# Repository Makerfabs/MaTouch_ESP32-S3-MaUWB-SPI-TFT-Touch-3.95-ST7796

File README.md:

# MaTouch ESP32-S3 MaUWB SPI TFT Touch 3.95" ST7796

## Introduction

The MaTouch 3.95 MaUWB is an ESP32-S3 development board featuring a 3.95-inch SPI display driven by the ST7796 controller, with a resolution of 480 x 320. It is equipped with an FT6236 capacitive touch controller, 16 MB Flash, and 8 MB PSRAM, providing responsive display and touch interaction for embedded applications.
The board integrates a MaUWB module for UWB ranging and indoor positioning applications. It also supports battery-powered operation, with an onboard lithium battery connector, charging circuit, battery level monitoring, and charge-status indicators, making it suitable for portable positioning terminals.
With its SPI display design, the board retains multiple GPIOs for secondary development through the expansion interface. It also includes a MicroSD card interface, native USB Type-C port, and USB-to-UART Type-C port for programming, debugging, and data storage.
Combining display, capacitive touch, UWB positioning, battery management, and expandable interfaces in one compact platform, the MaTouch 3.95 MaUWB is suitable for education, indoor positioning projects, embedded product development, and rapid prototyping.

Product Link: [MaTouch ESP32-S3 MaUWB SPI TFT Touch 3.95" ST7796](https://www.makerfabs.com/matouch-esp32-s3-mauwb-spi-tft-touch-3-95-st7796.html)

Wiki Link:  [MaTouch ESP32-S3 MaUWB SPI TFT Touch 3.95" ST7796](https://wiki.makerfabs.com/MaTouch%20ESP32_S3%20MaUWB%20SPI%20TFT%20Touch%203.95%27%27%20ST7796.html)

Example：1.[3.95_UWB_position](https://github.com/Makerfabs/MaTouch_ESP32-S3-MaUWB-SPI-TFT-Touch-3.95-ST7796#395_uwb_position)

## Features

- Controller: ESP32-S3 Chipset, 16MB Flash, 8MB PSRAM
- LCD: 3.95", 480X320 resolution 
- LCD Driver: ST7796
- LCD interface: SPI
- Touch Panel: Capacitive
- Touch Driver: FT6336U
- UWB: [MaUWB Chipset](https://www.makerfabs.com/mauwb-dw3000-chipset-ex-antenna-with-sma.html)
- RF band: CH5 (6489.6MHZ) 
- UWB rate: 850K/6.8M
- Max support: 8 Anchor 64 tags
- USB: 1 * USB_native, 1 *USB-to-UART
- USB-UART Driver: CH340K
- Power Supply: USB Type-C 5.0V(4.0V~5.25V)/ Lipo battery 
- Battery Charger
- Expansion interface: 2*JST1.25mm-4P
- LCD Backlight control: Yes

## Example

### 3.95_UWB_position

For details of this example, please refer to the [Wiki](https://wiki.makerfabs.com/MaTouch%20ESP32_S3%20MaUWB%20SPI%20TFT%20Touch%203.95%27%27%20ST7796.html#31-395_uwb_position) document.

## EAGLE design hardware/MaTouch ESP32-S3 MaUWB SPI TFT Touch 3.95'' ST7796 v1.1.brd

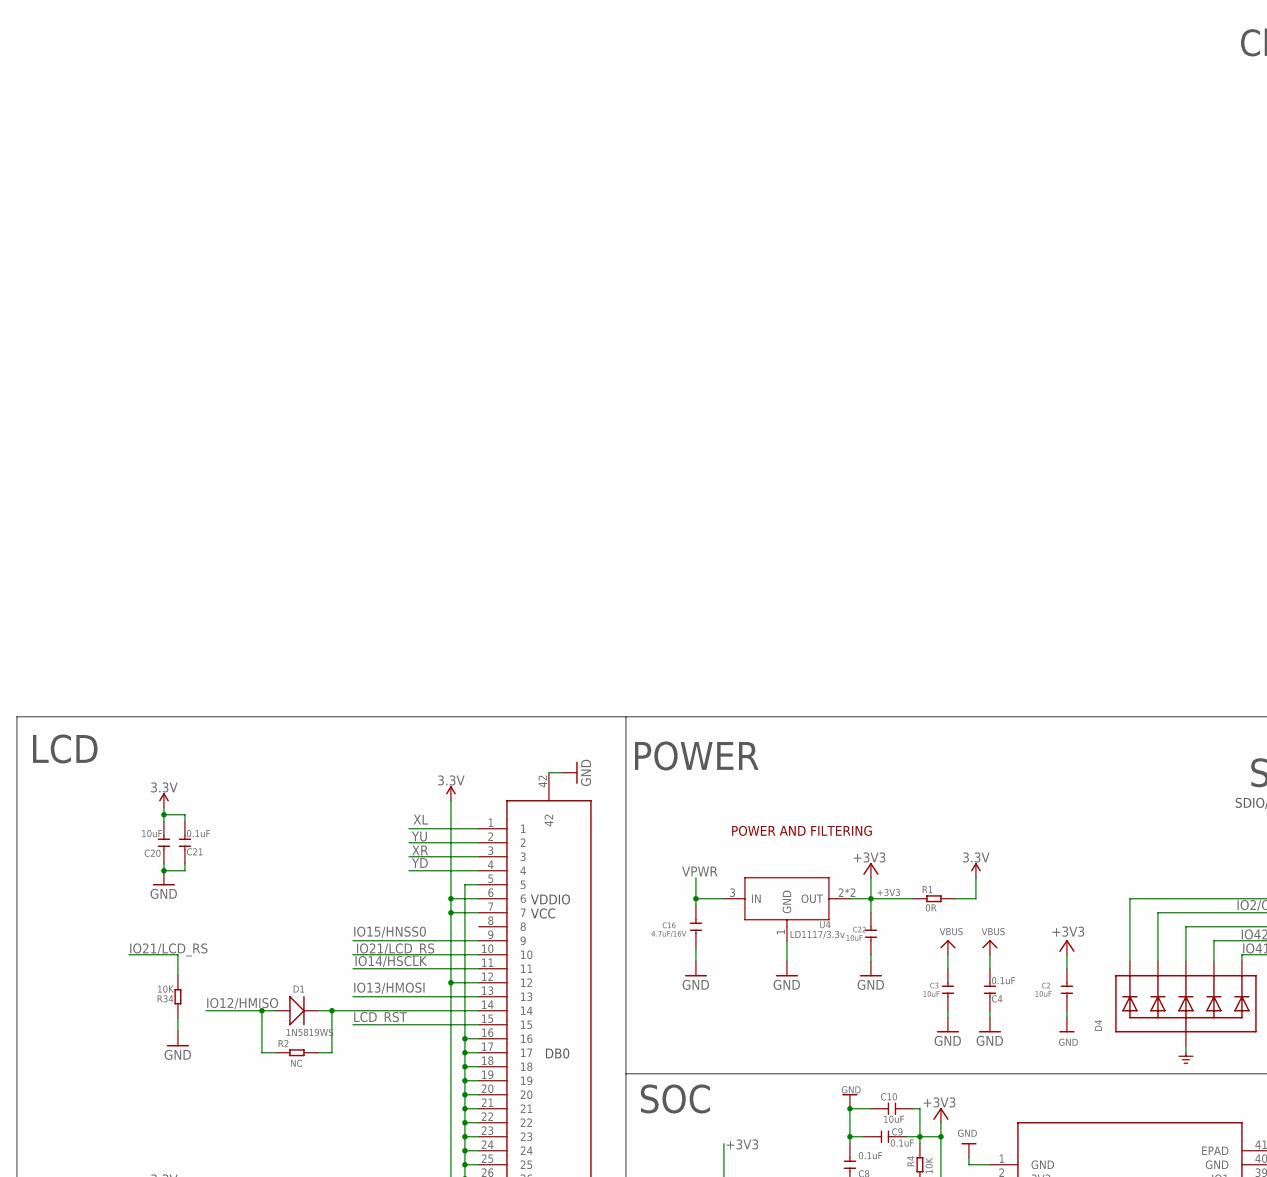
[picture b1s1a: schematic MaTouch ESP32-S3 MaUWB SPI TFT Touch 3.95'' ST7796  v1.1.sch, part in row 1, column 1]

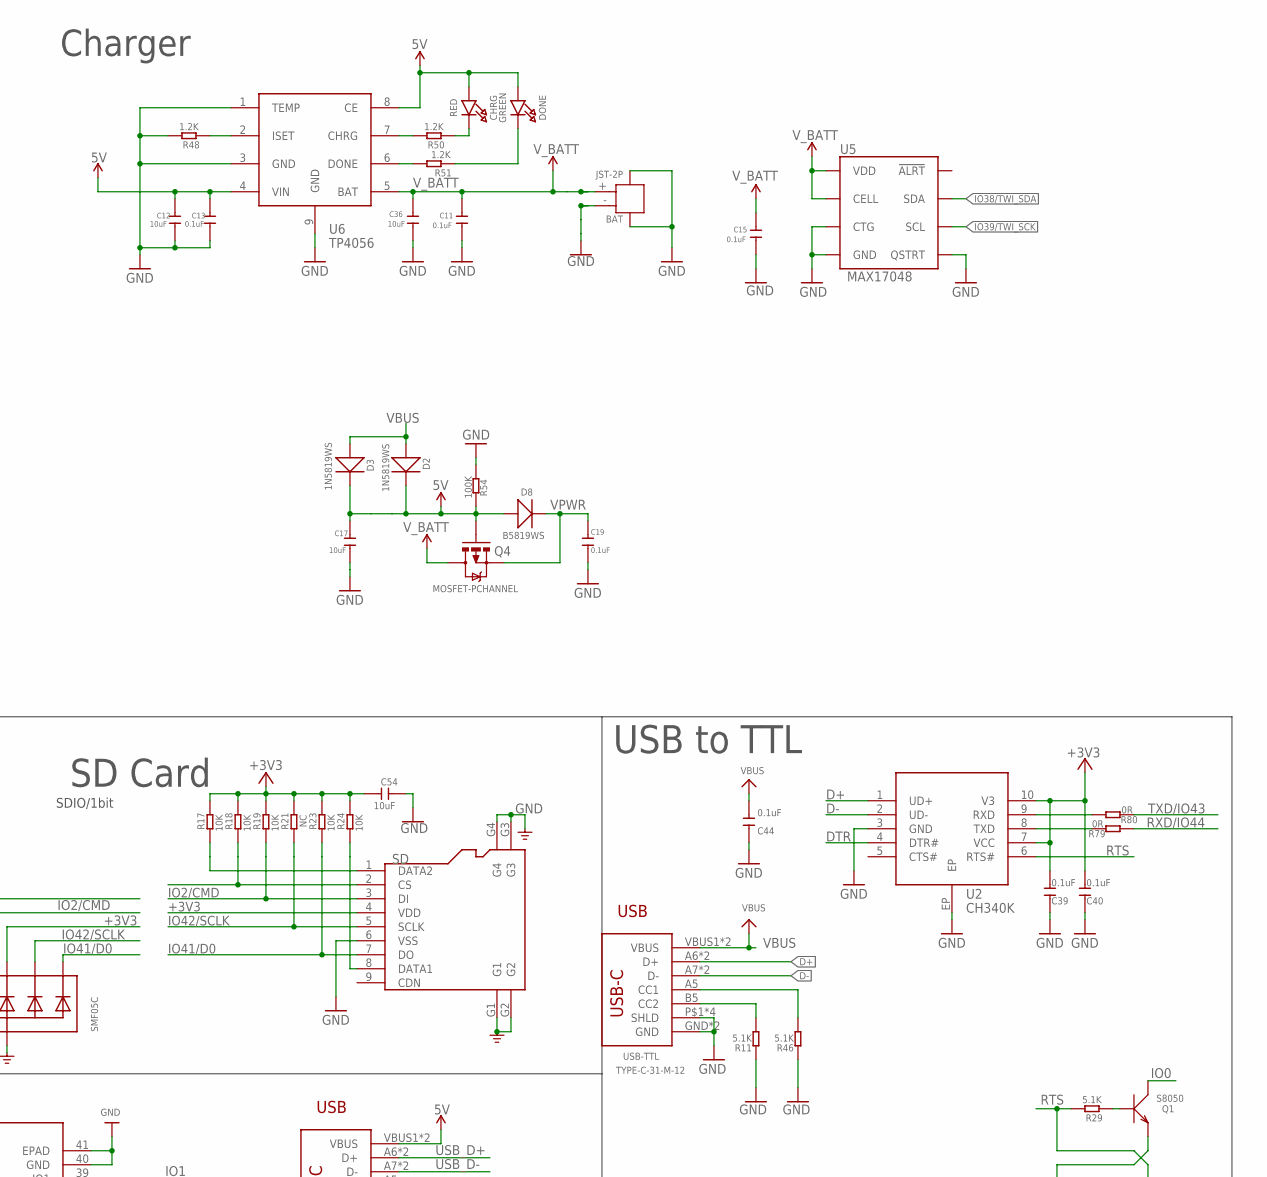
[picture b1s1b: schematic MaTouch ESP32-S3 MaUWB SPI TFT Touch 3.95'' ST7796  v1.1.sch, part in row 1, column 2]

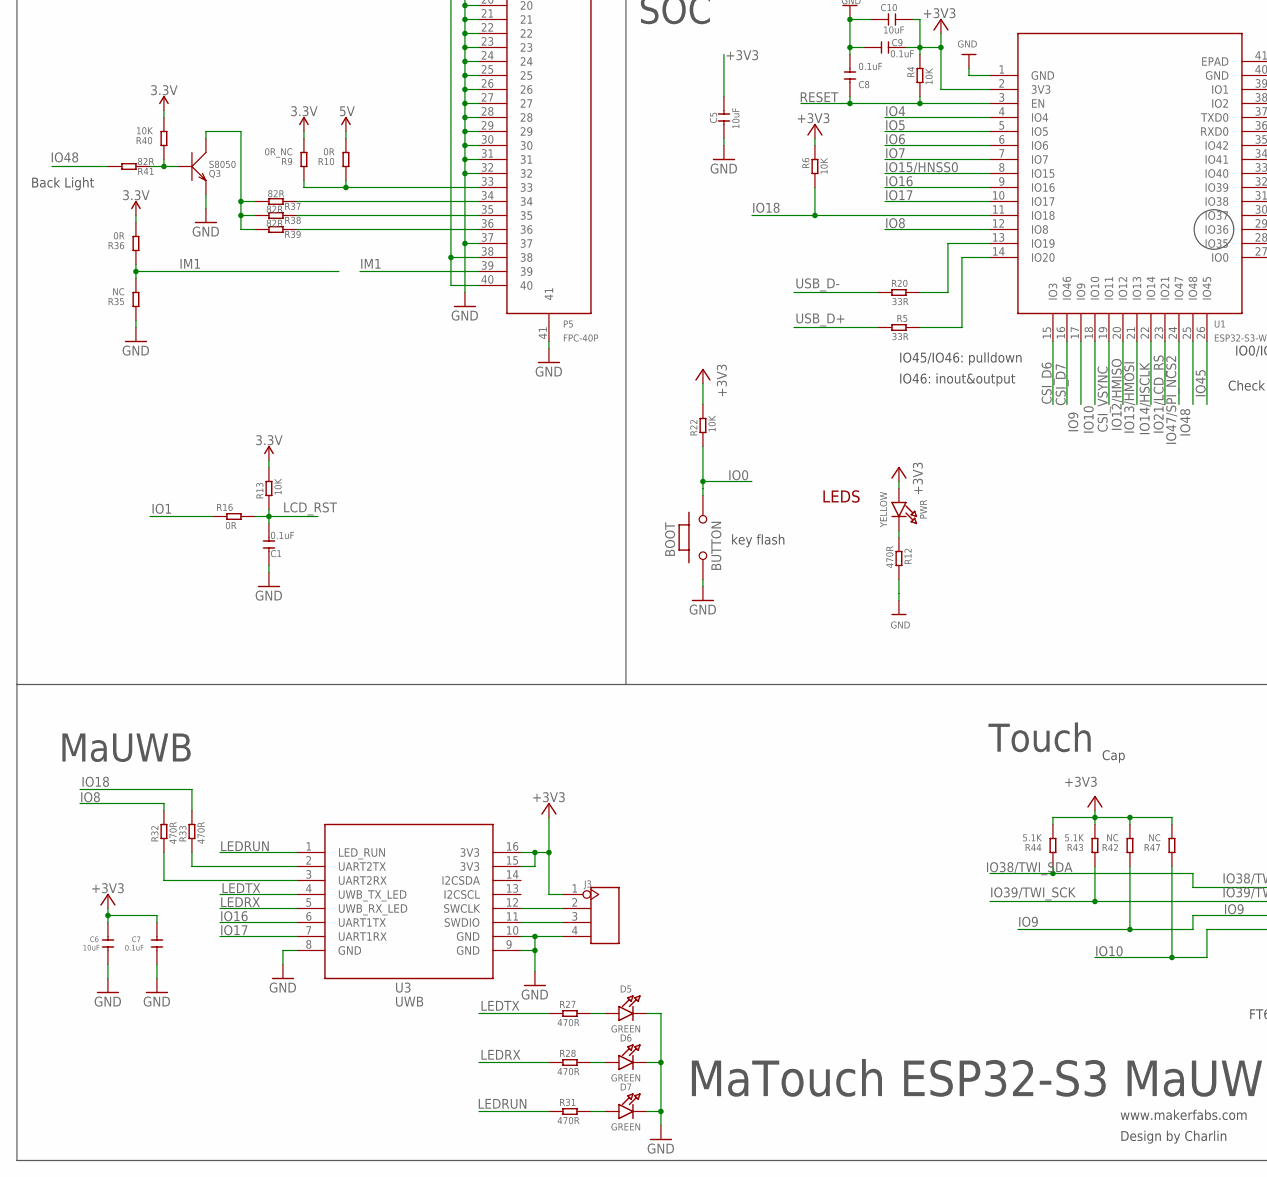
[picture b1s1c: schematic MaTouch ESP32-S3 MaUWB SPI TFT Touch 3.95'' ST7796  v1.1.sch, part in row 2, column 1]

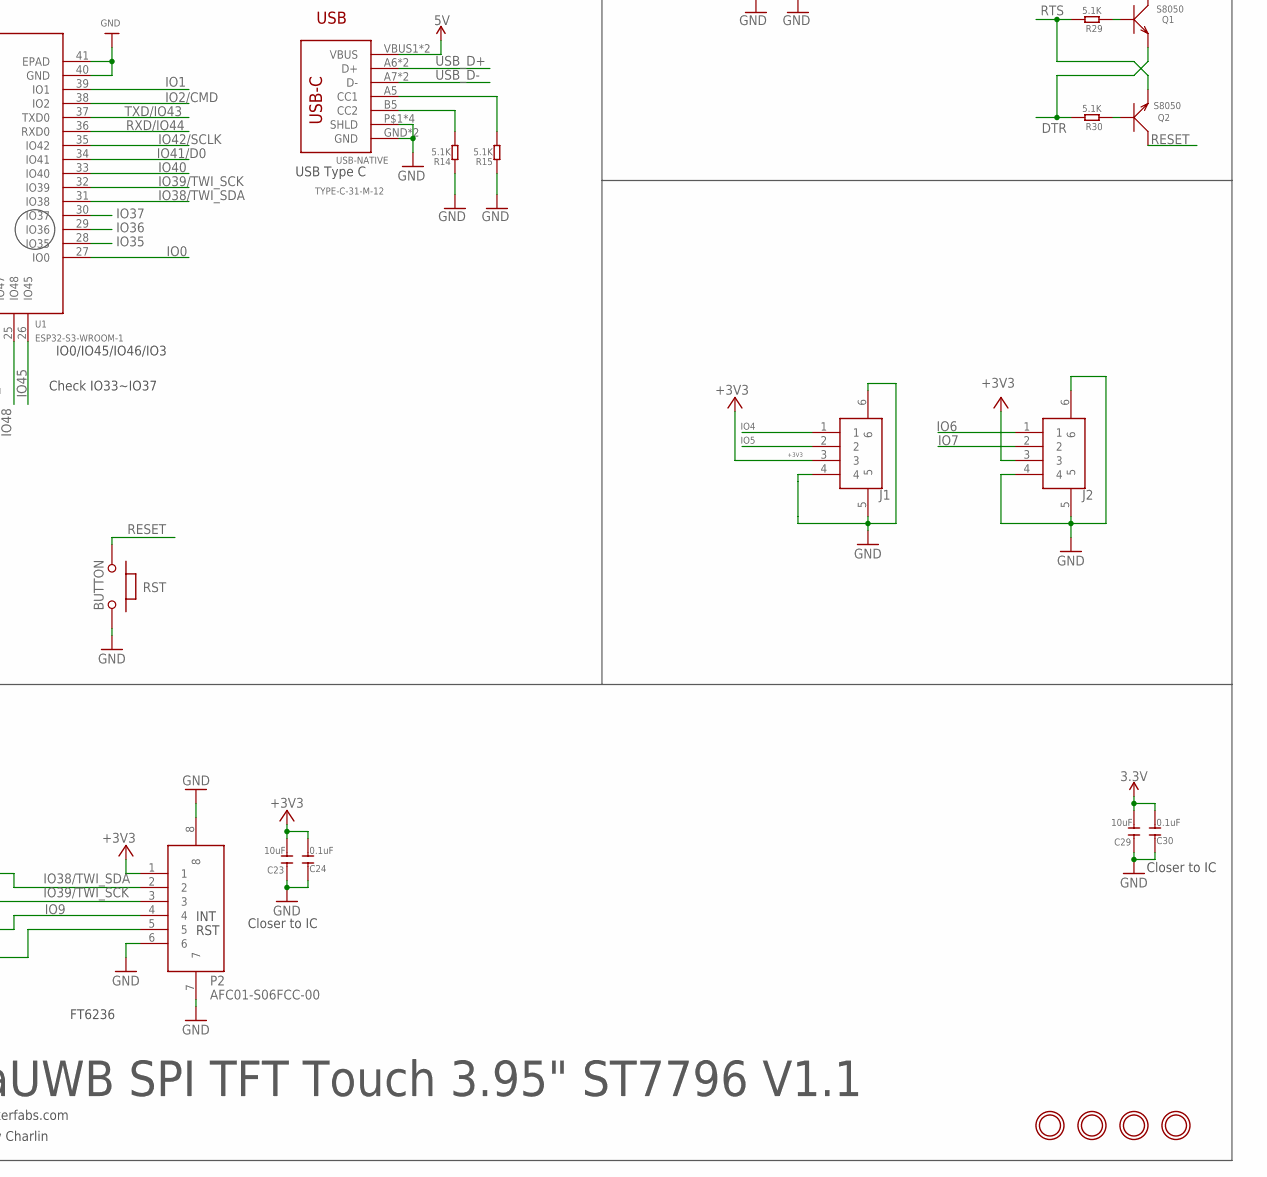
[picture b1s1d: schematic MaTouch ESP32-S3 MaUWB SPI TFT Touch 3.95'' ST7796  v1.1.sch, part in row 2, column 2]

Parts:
BAT: JST-2P; HW2-SMD-2.0-90D
BOOT: BUTTON; 157SW
C1, C4, C8, C9, C21, C24, C30, C39, C40, C44: 0.1uF; DISCRETE_C0603
C2, C3, C6, C12, C17, C22, C36: 10uF; C0603
C5, C10, C20, C23, C29, C54: 10uF; DISCRETE_C0603
C7, C11, C13, C15, C19: 0.1uF; C0603
C16: 4.7uF/16V; C0603
CHRG: RED; CHIPLED_0805_NOOUTLINE
D1, D2, D3: 1N5819WS; SOD323
D4: SMF05C; SOT363
D5, D6, D7: GREEN; CHIPLED_0805_NOOUTLINE
D8: B5819WS; SOD323
DONE: GREEN; CHIPLED_0805_NOOUTLINE
H1, H2, H3, H4: MICROBUILDER_MOUNTINGHOLE3.0THIN; MICROBUILDER_MOUNTINGHOLE_3.0_PLATEDTHIN
J1, J2: CON4-1.25P-SMD; SMD4-125P-1000L525W350H
J3: HEADER-4P-60/35MILROUND; 4P-65/35ROUND
P2: AFC01-S06FCC-00; SMD8-50P-740L535W
P5: FPC-40P; SMD42-50P-2560L490W
PWR: YELLOW; CHIPLED_0805_NOOUTLINE
Q1, Q2, Q3: S8050; SOT23
Q4: MOSFET-PCHANNEL; SOT23-3
R1, R16, R79, R80: 0R; R0603
R2, R21: NC; R0603
R4, R6, R13, R17, R18, R19, R22, R23, R24: 10K; R0603
R5, R20: 33R; R0603
R9: 0R_NC; DISCRETE_R0603
R10, R36: 0R; DISCRETE_R0603
R11, R14, R15, R43, R44, R46: 5.1K; DISCRETE_R0603
R12, R27, R28, R31, R32, R33: 470R; R0603
R29, R30: 5.1K; R0603
R34, R40: 10K; DISCRETE_R0603
R35, R42, R47: NC; DISCRETE_R0603
R37, R38, R39, R41: 82R; DISCRETE_R0603
R48, R50, R51: 1.2K; R0603
R54: 100K; R0603
RST: BUTTON; 157SW
SD: HOLDER-MICROSD-9P; 9P-SMD-W/-RING
U1: ESP32-S3-WROOM-1
U2: CH340K; ESOP-10-EP-150MIL
U3: UWB
U4: LD1117/3.3v; SOT89
U5: MAX17048; DFN-8
U6: TP4056; SOP8-1.27P
USB-NATIVE: TYPE-C-31-M-12
USB-TTL: TYPE-C-31-M-12

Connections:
5V: C12.1, C13.1, C17.1, CHRG.A, D2.-, D3.-, D8.+, DONE.A, Q4.1 (G), R10.2, R54.2, U6.4 (VIN), U6.8 (CE), USB-NATIVE.VBUS1 (VBUS), USB-NATIVE.VBUS2 (VBUS)
+3V3: C2.1, C5.1, C6.1, C7.1, C9.1, C10.1, C20.2, C21.2, C22.1, C23.2, C24.2, C29.2, C30.2, C39.2, C40.2, C54.2, D4.4 (C3), J1.3, J2.3, J3.1, P2.1, P5.6, P5.7, P5.12, P5.38, P5.40, PWR.A, R1.1, R1.2, R4.2, R6.2, R9.2, R13.2, R17.2, R18.2, R19.2, R21.2, R22.2, R23.2, R24.2, R36.2, R40.2, R42.2, R43.2, R44.2, R47.2, SD.4 (VDD), U1.2 (3V3), U2.7 (VCC), U2.10 (V3), U3.15 (3V3), U3.16 (3V3), U4.2 (OUT), U4.4 (OUT)
CSI_D6: U1.15 (IO3)
CSI_D7: U1.16 (IO46)
CSI_VSYNC: U1.19 (IO11)
D+: U2.1 (UD+), USB-TTL.A6 (D+), USB-TTL.B6 (D+)
D-: U2.2 (UD-), USB-TTL.A7 (D-), USB-TTL.B7 (D-)
DTR: Q1.2 (E), R30.2, U2.4 (DTR#)
GND: BAT.3, BAT.4, BAT.- (2), BOOT.1, C1.1, C2.2, C3.2, C4.1, C5.2, C6.2, C7.2, C8.2, C9.2, C10.2, C11.2, C12.2, C13.2, C15.2, C16.2, C17.2, C19.2, C20.1, C21.1, C22.2, C23.1, C24.1, C29.1, C30.1, C36.2, C39.1, C40.1, C44.1, C54.1, D4.2 (A), D5.C, D6.C, D7.C, J1.4, J1.5, J1.6, J2.4, J2.5, J2.6, J3.4, P2.6, P2.7, P2.8, P5.5, P5.16, P5.17, P5.18, P5.19, P5.20, P5.21, P5.22, P5.23, P5.24, P5.25, P5.26, P5.27, P5.28, P5.29, P5.30, P5.31, P5.32, P5.37, P5.41, P5.42, Q3.2 (E), R11.1, R12.2, R14.1, R15.1, R34.1, R35.1, R46.1, R48.2, R54.1, RST.1, SD.6 (VSS), SD.G1, SD.G2, SD.G3, SD.G4, U1.1 (GND), U1.40 (GND), U1.41 (EPAD), U2.3 (GND), U2.EP, U3.8 (GND), U3.9 (GND), U3.10 (GND), U4.1 (GND), U5.1 (CTG), U5.4 (GND), U5.6 (QSTRT), U5.9 (GND), U6.1 (TEMP), U6.3 (GND), U6.9 (GND), USB-NATIVE.GND, USB-NATIVE.GND2 (GND), USB-NATIVE.P$1 (SHLD), USB-NATIVE.P$2 (SHLD), USB-NATIVE.P$3 (SHLD), USB-NATIVE.P$4 (SHLD), USB-TTL.GND, USB-TTL.GND2 (GND), USB-TTL.P$1 (SHLD), USB-TTL.P$2 (SHLD), USB-TTL.P$3 (SHLD), USB-TTL.P$4 (SHLD)
IM1: P5.39, R35.2, R36.1
IO0: BOOT.2, Q1.3 (C), R22.1, U1.27 (IO0)
IO1: R16.1, U1.39 (IO1)
IO1/CS: D4.1 (C1), R18.1, SD.2 (CS)
IO2/CMD: D4.3 (C2), R19.1, SD.3 (DI), U1.38 (IO2)
IO4: J1.1, U1.4 (IO4)
IO5: J1.2, U1.5 (IO5)
IO6: J2.1, U1.6 (IO6)
IO7: J2.2, U1.7 (IO7)
IO8: R32.2, U1.12 (IO8)
IO9: P2.4, R42.1, U1.17 (IO9)
IO10: P2.5, R47.1, U1.18 (IO10)
IO12/HMISO: D1.+, R2.1, U1.20 (IO12)
IO13/HMOSI: P5.13, U1.21 (IO13)
IO14/HSCLK: P5.11, U1.22 (IO14)
IO15/HNSS0: P5.9, U1.8 (IO15)
IO16: U1.9 (IO16), U3.6 (UART1TX)
IO17: U1.10 (IO17), U3.7 (UART1RX)
IO18: R6.1, R33.2, U1.11 (IO18)
IO21/LCD_RS: P5.10, R34.2, U1.23 (IO21)
IO35: U1.28 (IO35)
IO36: U1.29 (IO36)
IO37: U1.30 (IO37)
IO38/TWI_SDA: P2.2, R44.1, U1.31 (IO38), U5.8 (SDA)
IO39/TWI_SCK: P2.3, R43.1, U1.32 (IO39), U5.7 (SCL)
IO40: U1.33 (IO40)
IO41/D0: D4.6 (C5), R23.1, SD.7 (DO), U1.34 (IO41)
IO42/SCLK: D4.5 (C4), R21.1, SD.5 (SCLK), U1.35 (IO42)
IO45: U1.26 (IO45)
IO47/SPI_NCS2: U1.24 (IO47)
IO48: R41.2, U1.25 (IO48)
LCD_RST: C1.2, P5.15, R13.1, R16.2
LEDRUN: R31.1, U3.1 (LED_RUN)
LEDRX: R28.1, U3.5 (UWB_RX_LED)
LEDTX: R27.1, U3.4 (UWB_TX_LED)
unnamed: R46.2, USB-TTL.A5 (CC1)
unnamed: D5.A, R27.2
unnamed: D6.A, R28.2
unnamed: D1.-, P5.14, R2.2
unnamed: Q2.1 (B), R30.1
unnamed: D7.A, R31.2
unnamed: PWR.C, R12.1
unnamed: Q1.1 (B), R29.1
unnamed: R51.2, U6.6 (DONE)
unnamed: R33.1, U3.2 (UART2TX)
unnamed: R32.1, U3.3 (UART2RX)
unnamed: R48.1, U6.2 (ISET)
unnamed: R50.2, U6.7 (CHRG)
unnamed: R15.2, USB-NATIVE.A5 (CC1)
unnamed: R20.2, U1.13 (IO19)
unnamed: R5.2, U1.14 (IO20)
unnamed: R14.2, USB-NATIVE.B5 (CC2)
unnamed: R11.2, USB-TTL.B5 (CC2)
unnamed: CHRG.C, R50.1
unnamed: P5.34, R37.1
unnamed: P5.35, R38.1
unnamed: P5.36, R39.1
unnamed: Q3.1 (B), R40.1, R41.1
unnamed: Q3.3 (C), R37.2, R38.2, R39.2
unnamed: P5.33, R9.1, R10.1
unnamed: J3.3, U3.11 (SWDIO)
unnamed: J3.2, U3.12 (SWCLK)
unnamed: DONE.C, R51.1
unnamed: R80.2, U2.9 (RXD)
unnamed: R79.2, U2.8 (TXD)
unnamed: R17.1, SD.1 (DATA2)
unnamed: R24.1, SD.8 (DATA1)
RESET: C8.1, Q2.3 (C), R4.1, RST.2, U1.3 (EN)
RTS: Q2.2 (E), R29.2, U2.6 (RTS#)
RXD/IO44: R79.1, U1.36 (RXD0)
TXD/IO43: R80.1, U1.37 (TXD0)
USB_D+: R5.1, USB-NATIVE.A6 (D+), USB-NATIVE.B6 (D+)
USB_D-: R20.1, USB-NATIVE.A7 (D-), USB-NATIVE.B7 (D-)
VBUS: C3.1, C4.2, C44.2, D2.+, D3.+, USB-TTL.VBUS1 (VBUS), USB-TTL.VBUS2 (VBUS)
VPWR: C16.1, C19.1, D8.-, Q4.2 (S), U4.3 (IN)
V_BATT: BAT.+ (1), C11.1, C15.1, C36.1, Q4.3 (D), U5.2 (CELL), U5.3 (VDD), U6.5 (BAT)
XL: P5.1
XR: P5.3
YD: P5.4
YU: P5.2

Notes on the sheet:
www.makerfabs.com
Design by Charlin
LEDS
POWER AND FILTERING
key flash
MaTouch ESP32-S3 MaUWB SPI TFT Touch 3.95" ST7796 V1.1
POWER
USB to TTL
SD Card
Closer to IC
Back Light
IO45/IO46: pulldown
IO46: inout&output
USB
USB Type C
IO0/IO45/IO46/IO3
Check IO33~IO37
LCD
SOC
VDDIO
VCC
DB0
SDIO/1bit
MaUWB
FT6236
Touch
RST
INT
Cap
Charger

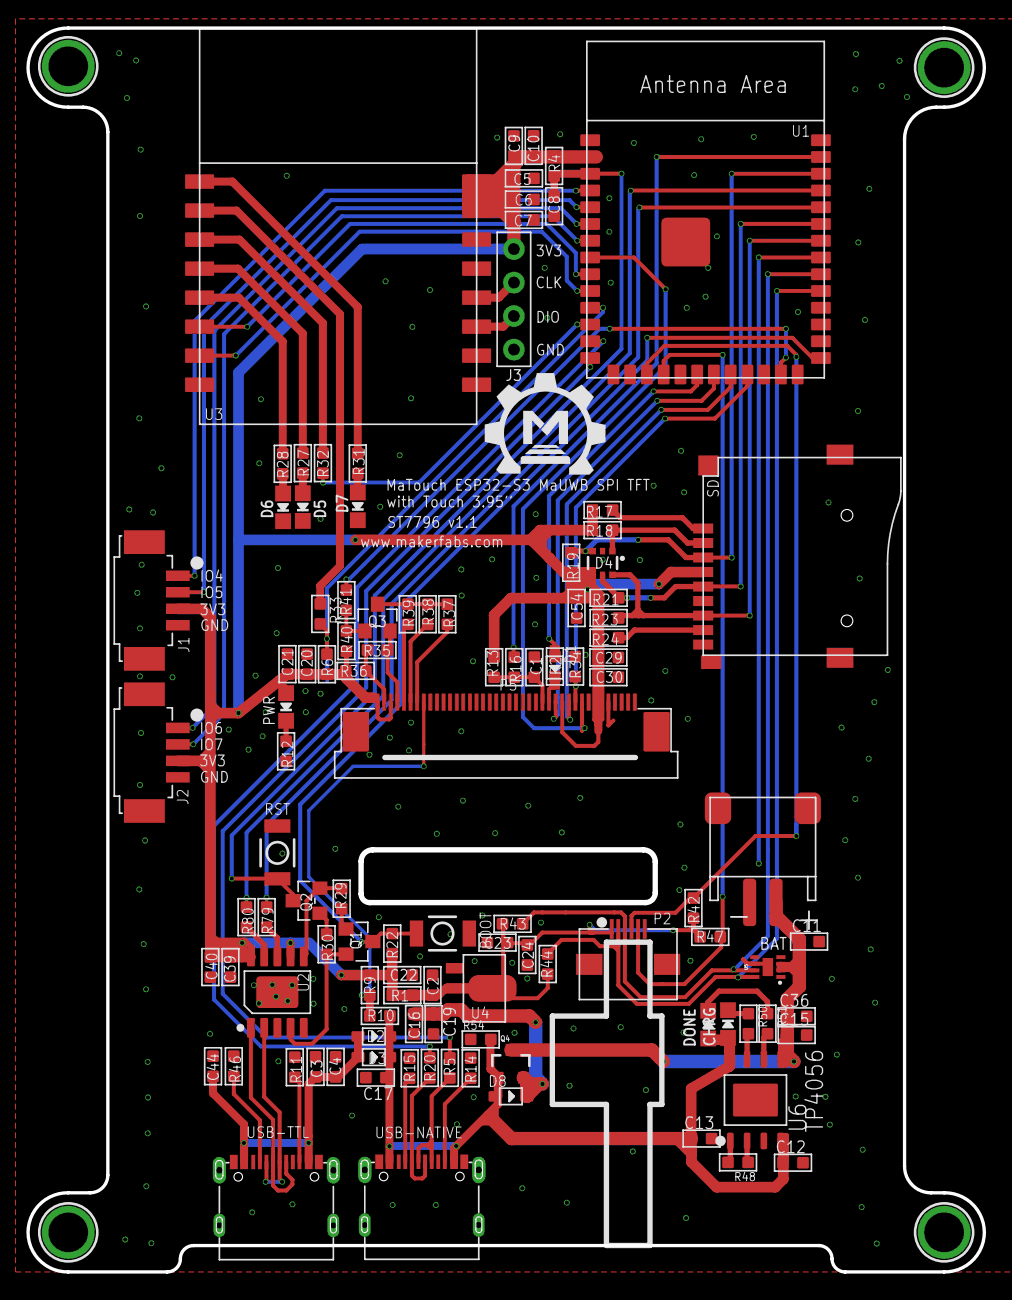
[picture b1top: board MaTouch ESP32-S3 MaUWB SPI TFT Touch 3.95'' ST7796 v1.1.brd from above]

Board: 2 copper layers, 72.5 x 94.3 mm, 113 parts (0 on the bottom side), 76 nets.

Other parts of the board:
U$1: MAKERFABS_0.3

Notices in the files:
parts and their libraries:
SparkFun-PowerSymbols: Licensing: Creative Commons ShareAlike 4.0 International - https://creativecommons.org/licenses/by-sa/4.0
microbuilder: This work is placed in the public domain, and may be freely used for commercial and non-commercial work with the following conditions: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
